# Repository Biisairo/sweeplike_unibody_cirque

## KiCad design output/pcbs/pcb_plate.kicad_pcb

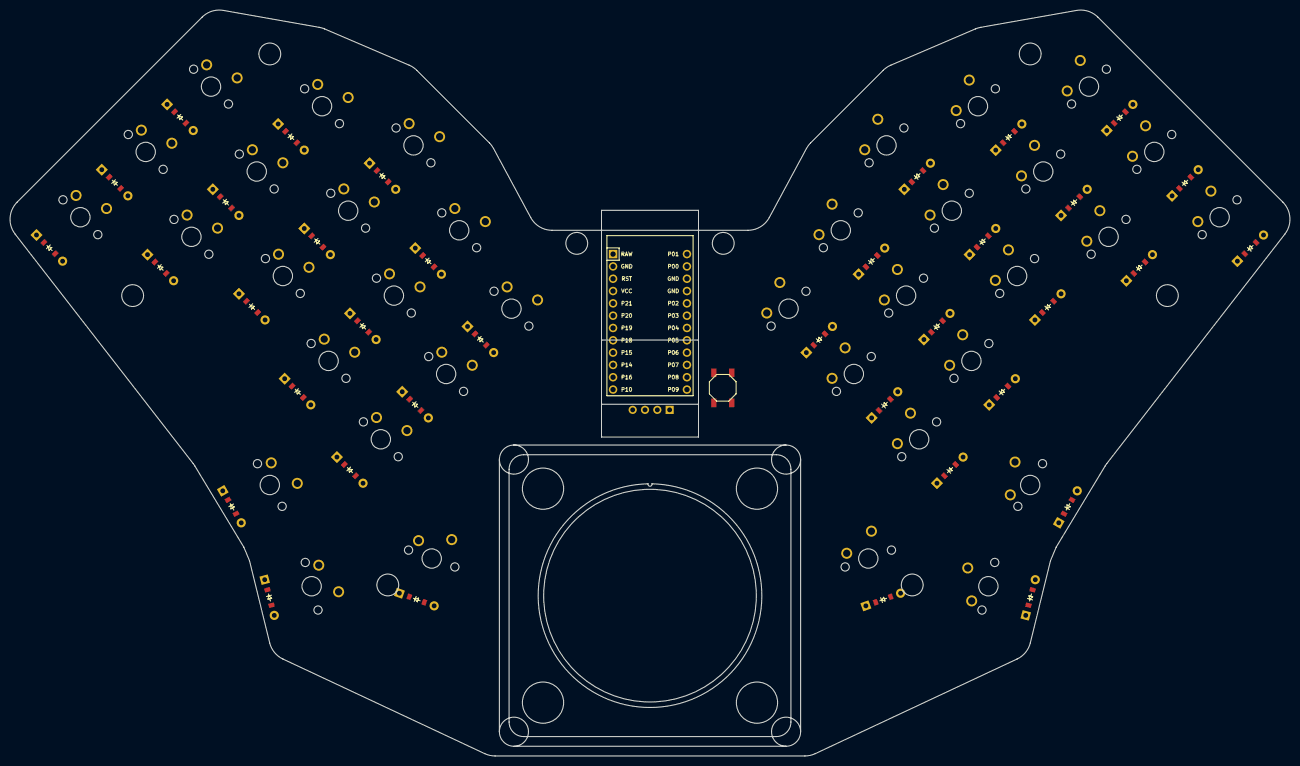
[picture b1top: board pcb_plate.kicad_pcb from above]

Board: 2 copper layers, 264.0 x 153.8 mm, 75 parts (0 on the bottom side), 54 nets, no tracks yet.

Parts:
B1: SW_TACT_ALPS_SKQGABE010
D1, D2, D3, D4, D5, D6, D7, D8, D9, D10, D11, D12, D13, D14, D15, D16, D17, D18, D19, D20, D21, D22, D23, D24, D25, D26, D27, D28, D29, D30, D31, D32, D33, D34, D35, D36: ComboDiode
MCU1: ProMicro
OLED1: OLED; OLED_headers
S1, S2, S3, S4, S5, S6, S7, S8, S9, S10, S11, S12, S13, S14, S15, S16, S17, S18, S19, S20, S21, S22, S23, S24, S25, S26, S27, S28, S29, S30, S31, S32, S33, S34, S35, S36: MX

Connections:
GND: B1.1, MCU1.2, MCU1.15, MCU1.16, OLED1.1
P2: MCU1.17, OLED1.4
P3: MCU1.18, OLED1.3
P4: MCU1.19, S1.1, S2.1, S3.1, S19.1, S20.1, S21.1
P5: MCU1.20, S4.1, S5.1, S6.1, S16.1, S22.1, S23.1, S24.1, S34.1
P6: D21.1, D24.1, D27.1, D30.1, D33.1, MCU1.21
P7: D20.1, D23.1, D26.1, D29.1, D32.1, MCU1.22
P8: D19.1, D22.1, D25.1, D28.1, D31.1, MCU1.23
P9: D34.1, D35.1, D36.1, MCU1.24
P10: D16.1, D17.1, D18.1, MCU1.12
P14: D2.1, D5.1, D8.1, D11.1, D14.1, MCU1.10
P15: D3.1, D6.1, D9.1, D12.1, D15.1, MCU1.9
P16: D1.1, D4.1, D7.1, D10.1, D13.1, MCU1.11
P18: MCU1.8, S7.1, S8.1, S9.1, S17.1, S25.1, S26.1, S27.1, S35.1
P19: MCU1.7, S10.1, S11.1, S12.1, S18.1, S28.1, S29.1, S30.1, S36.1
P20: MCU1.6, S13.1, S14.1, S15.1, S31.1, S32.1, S33.1
RST: B1.2, MCU1.3
VCC: MCU1.4, OLED1.2
index_bottom: D10.2, S10.2
index_home: D11.2, S11.2
index_top: D12.2, S12.2
inner_bottom: D13.2, S13.2
inner_home: D14.2, S14.2
inner_top: D15.2, S15.2
layer_cluster: D16.2, S16.2
middle_bottom: D7.2, S7.2
middle_home: D8.2, S8.2
middle_top: D9.2, S9.2
mirror_index_bottom: D28.2, S28.2
mirror_index_home: D29.2, S29.2
mirror_index_top: D30.2, S30.2
mirror_inner_bottom: D31.2, S31.2
mirror_inner_home: D32.2, S32.2
mirror_inner_top: D33.2, S33.2
mirror_layer_cluster: D34.2, S34.2
mirror_middle_bottom: D25.2, S25.2
mirror_middle_home: D26.2, S26.2
mirror_middle_top: D27.2, S27.2
mirror_one_one: D36.2, S36.2
mirror_pinky_bottom: D19.2, S19.2
mirror_pinky_home: D20.2, S20.2
mirror_pinky_top: D21.2, S21.2
mirror_ring_bottom: D22.2, S22.2
mirror_ring_home: D23.2, S23.2
mirror_ring_top: D24.2, S24.2
mirror_space_cluster: D35.2, S35.2
one_one: D18.2, S18.2
pinky_bottom: D1.2, S1.2
pinky_home: D2.2, S2.2
pinky_top: D3.2, S3.2
ring_bottom: D4.2, S4.2
ring_home: D5.2, S5.2
ring_top: D6.2, S6.2
space_cluster: D17.2, S17.2

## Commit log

2024-04-30 second commit
